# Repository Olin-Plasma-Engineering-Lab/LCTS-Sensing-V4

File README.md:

# LCTS-Sensing-V4

## Purpose
The project in this repo is used to control a LabJack T7 data acquisition device. Our uses require analog pins for measuring signals from RVDTs, thermocouples, etc. and digital pins for controlling a servo using PWM.

## Set Up
Using the scripts requires the LabJack drivers (https://support.labjack.com/docs/ljm-software-installer-downloads-t4-t7-t8-digit).

The Python implementation also requires Python 3.9 or newer.

## Python Implementation

### Environment
Create a virtual environment using `python -m venv sensing` to create an environment called `sensing`. Do this in the directory where this repo exists. Once the environment is created it does not need to be created again unless it gets deleted. You may have to re-enter the environment when you open a new terminal/command prompt though.

Enter the environment:
- For Windows: `sensing\Scripts\activate`
- For Linux/macOS: `source sensing/bin/activate`

Run `pip install -r calibrate_py/requirements.txt` to install dependencies. This also only has to be done once after creating and entering the environment for the first time.

### Running

Two entry points are available. They share the same hardware code, so anything you can do from one you can do from the other.

**GUI (recommended).** Run `python run_gui.py` to launch the desktop application. The window has two tabs:

- **Setup** — pick the position pin, thermocouple pins, PWM DIO, and CJC source; connect to the device; choose a mode (Take data, Interactive, Timed sequence, or CSV import) and configure it.
- **Live data** — shows the live plot, current angle, CJC temperature, sample count, and the CSV file name. Start / Stop controls live here. Up / Down hold-to-move buttons appear in Interactive mode; a Continue button appears in CSV mode for stepping past pause-between-step prompts. Arrow keys also drive the servo in Interactive mode when the window has focus.

The GUI auto-switches to the Live data tab when capture starts so the plot is immediately visible. Switching back to Setup mid-run does not stop the capture.

**CLI.** Run `python run_calibrate.py` for a text-based interface that walks through the same modes via prompts. Useful on machines without a desktop environment, or for scripted runs.

### Cross-platform notes

The GUI uses [PySide6](https://pypi.org/project/PySide6/) and the CLI uses [pynput](https://pypi.org/project/pynput/) for keyboard input. Both are cross-platform but each has small caveats:

- **macOS:** the first time the CLI runs, you'll need to grant your terminal application "Input Monitoring" / "Accessibility" permission in System Settings, otherwise hold-to-move arrow-key detection will silently fail. The GUI doesn't need this since it captures arrow keys through Qt.
- **Linux:** the CLI's interactive arrow-key mode requires an X server (or a uinput-capable backend). On a headless box, use the GUI's Interactive mode (it works wherever Qt runs) or the timed/CSV modes.
- **Windows:** both work out of the box.

### CSV step format (CSV import mode)
One step per line, two columns:

```
up,2.5
down,2.5
zero,1.0
135,3.0
```

The first field is either a direction keyword (`up`, `down`, `zero`) or an explicit integer angle. The second field is the duration in seconds. Between steps the script pauses with the servo disabled until you press Continue (GUI) or Enter (CLI), or Esc to abort.

### Cold-junction compensation (CJC)
When more than one input pin is configured, the script treats the first pin as the position sensor and any remaining pins as K-type thermocouples, converting their voltages to degrees Celsius using NIST ITS-90 polynomials.

The cold-junction temperature is read **live** from the T7 by default (`TEMPERATURE_DEVICE_K`). A -3 C offset is applied to match the screw-terminal temperature, since the T7's internal sensor reads a few degrees warmer than the terminals during steady-state operation. The CJC source can be changed in the GUI (Setup → Device configuration) or in the `Config` block of `calibrate.py`:

- `"device"` (default): T7 internal sensor. Best for thermocouples wired to AIN0-AIN3 directly.
- `"air"`: T7 ambient estimate. Best for thermocouples wired to a CB37 expansion board.
- a fixed float (e.g. `25.0`): static CJC value in degrees C.

When thermocouple conversion is enabled, the output CSV gains a `CJC_C` column so the cold-junction temperature can be checked offline.

### Project layout

```
LCTS-Sensing-V4/
├── run_gui.py                  GUI runner
├── run_calibrate.py            CLI runner
├── requirements.txt
├── calibrate_py/
│   ├── calibrate.py            CLI orchestration
│   ├── data_acquisition.py     Sampling, CJC, CSV logging
│   ├── labjack_device.py       Device open / close / per-pin range & resolution
│   ├── servo_calibration.py    PWM math for servo control
│   ├── thermocouples.py        K-type ITS-90 conversion
│   ├── live_plot.py            Standalone live CSV plotter (used by the CLI)
│   └── gui/                    PySide6 GUI
│       ├── main_window.py      Window, state machine, mode dispatch
│       ├── live_plot_widget.py Embedded matplotlib canvas
│       ├── step_table.py       Angle and direction step tables; CSV parser
│       └── constants.py        Shared defaults (sample period, etc.)
```

## C# Implementation (archive)
The C# implementation is the original attempt for interfacing with the LabJack. While it works reliably, it is harder to add features in C# and isn't immediately compatible with Mac. Further implementations are in Python.

### Implementation
The project contains a `Device` namespace containing helpers for various control of the device:

#### `LabJackDevice`
This contains helpers for establishing a connection with the device, configuring pins for analog reading, disposing of the device, etc.

#### `DataAcquisition`
This contains helpers for reading + printing data, creating output files, etc.

#### `ServoCalibration`
This contains helpers for controlling a servo connected to the T7. It produces PWM signals that can be used to control a servo.

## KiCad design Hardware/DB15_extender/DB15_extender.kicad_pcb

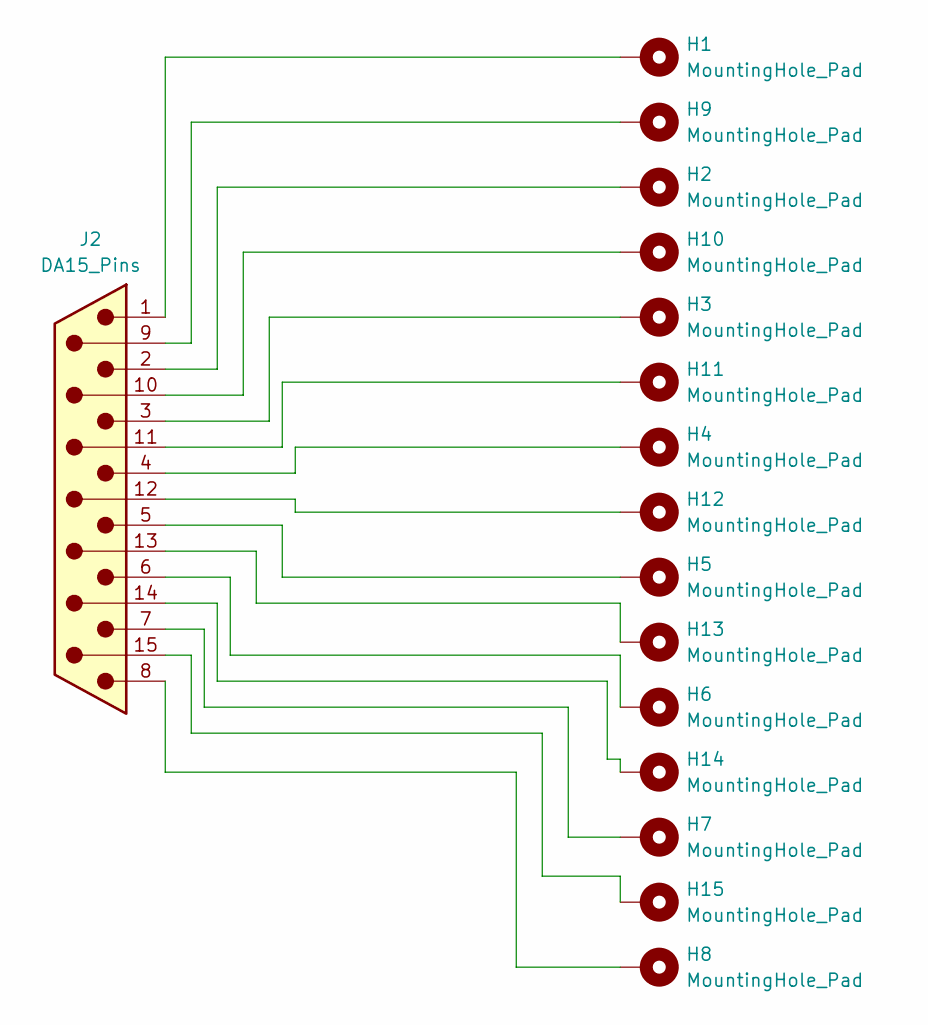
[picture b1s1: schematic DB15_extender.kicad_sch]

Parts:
H1, H2, H3, H4, H5, H6, H7, H8, H9, H10, H11, H12, H13, H14, H15: MountingHole_Pad; PinHeader_1x01_P2.54mm_Vertical
J2: DA15_Pins; DSUB-15_Pins_Horizontal_P2.77x2.84mm_EdgePinOffset9.40mm

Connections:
unnamed: H1.1, J2.1
unnamed: H2.1, J2.2
unnamed: H3.1, J2.3
unnamed: H4.1, J2.4
unnamed: H5.1, J2.5
unnamed: H6.1, J2.6
unnamed: H7.1, J2.7
unnamed: H8.1, J2.8
unnamed: H9.1, J2.9
unnamed: H10.1, J2.10
unnamed: H12.1, J2.12
unnamed: H13.1, J2.13
unnamed: H14.1, J2.14
unnamed: H15.1, J2.15
unnamed: H11.1, J2.11 (P111)

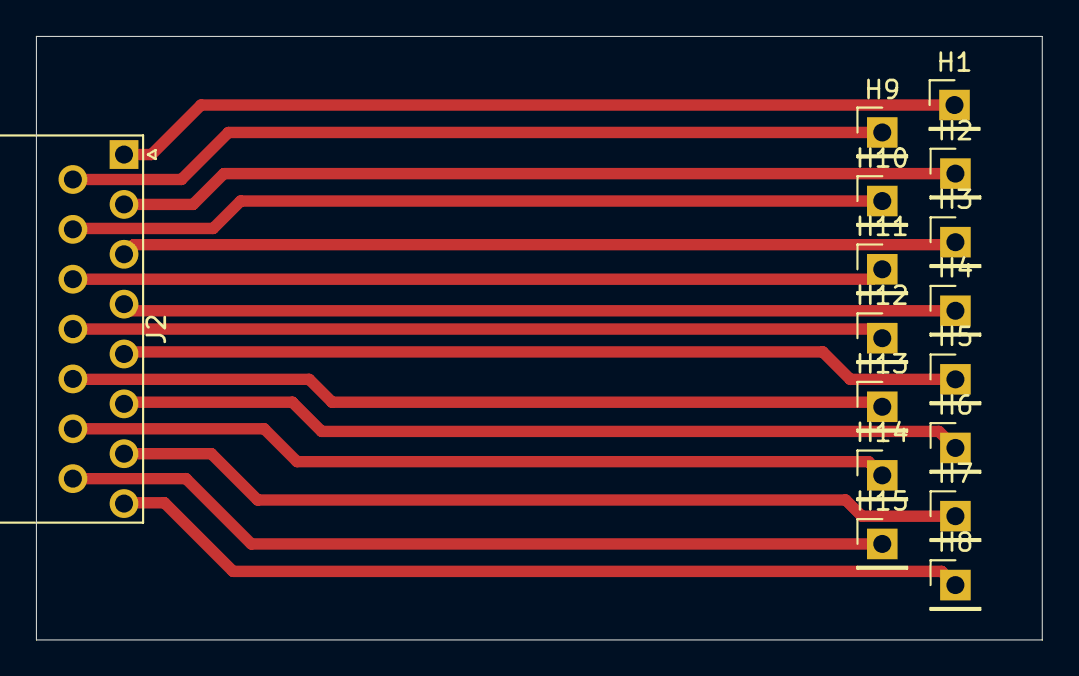
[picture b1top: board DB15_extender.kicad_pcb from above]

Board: 2 copper layers, 55.9 x 33.5 mm, 16 parts (0 on the bottom side), 15 nets.

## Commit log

2025-09-17 Add starter script for reading values from an RVDT
    Script adapted from example code from the LabJack website
2025-09-18 add start to calibration, helper functions, other
2025-09-22 Refactor to shorten main scripts
2025-09-25 Fix data collecting bugs
2025-09-25 Modify how data is saved to csv
2025-09-28 Continue implementation and refactor for calibrate
2025-09-30 Data collection bug fixes
2025-10-02 Fix PWM control methods
2025-10-23 Add README and other updates
2025-11-06 Add functionality to set number of pins used
2025-11-18 Process fixes, make file addition
2026-01-26 Add calibration functionality for 360 degree servo
2026-02-20 Refactor calibrate and read into one program
2026-03-12 Add Python implementation of calibration script
2026-03-14 commit thrust stand analysis file
2026-03-30 Add new functionality to python implementation
    Thermocouples now get plotted alongside RVIT output
    Thermocouple raw data converted to temperature before being plotted
2026-04-02 Add start of connector board and other code changes
2026-04-02 Add requirements.txt for python implementation
2026-04-02 Update README to include python implementation
2026-04-02 Restructure files
2026-04-02 Add more instructions for python set up
2026-04-27 Refactor python implementation for better function
2026-04-28 Add gui
2026-05-01 Update README to contain info about the gui
